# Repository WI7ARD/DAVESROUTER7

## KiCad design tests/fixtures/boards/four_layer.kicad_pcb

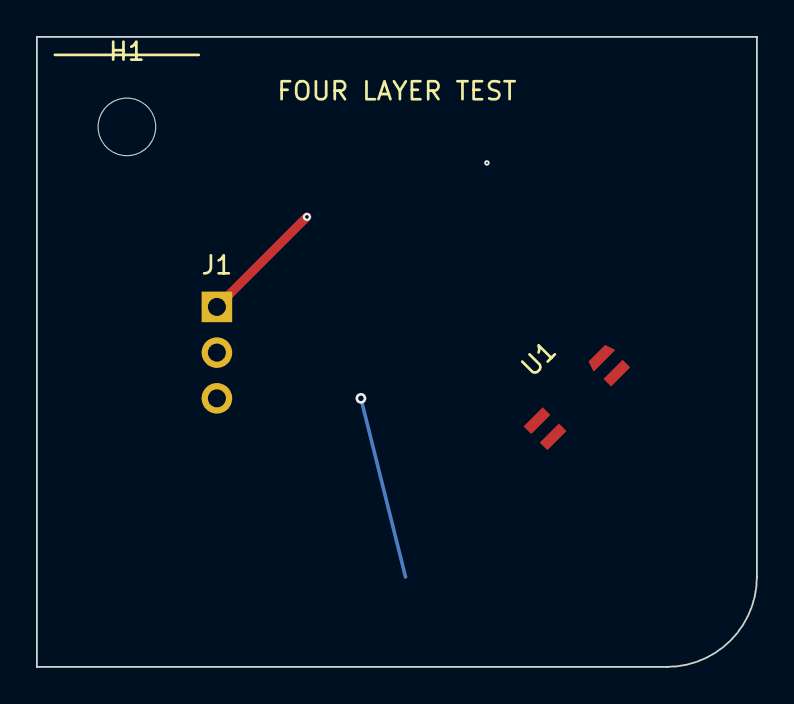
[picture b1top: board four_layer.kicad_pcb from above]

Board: 4 copper layers, 40.0 x 35.0 mm, 4 parts (1 on the bottom side), 3 nets.

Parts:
H1: MountingHole; MountingHole_3.2mm_M3
J1: Conn_01x03; PinHeader_1x03_P2.54mm_Vertical
R2: 4k7; R_0402_1005Metric
U1: SENSOR; SOIC-4_Test

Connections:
+3V3: J1.2, R2.2, U1.1
/DATA: J1.3, R2.1, U1.3
GND: J1.1, U1.2

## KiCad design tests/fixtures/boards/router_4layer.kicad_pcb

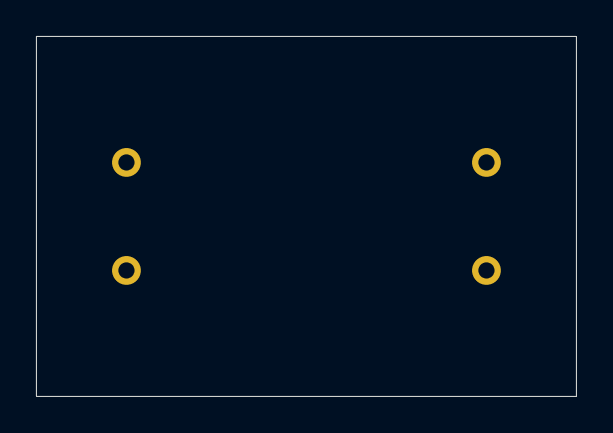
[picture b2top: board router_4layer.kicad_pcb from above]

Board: 4 copper layers, 30.0 x 20.0 mm, 4 parts (0 on the bottom side), 2 nets, no tracks yet.

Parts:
A1, A2: TP
B1, B2: TP

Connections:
N1: A1.1, A2.1
N2: B1.1, B2.1

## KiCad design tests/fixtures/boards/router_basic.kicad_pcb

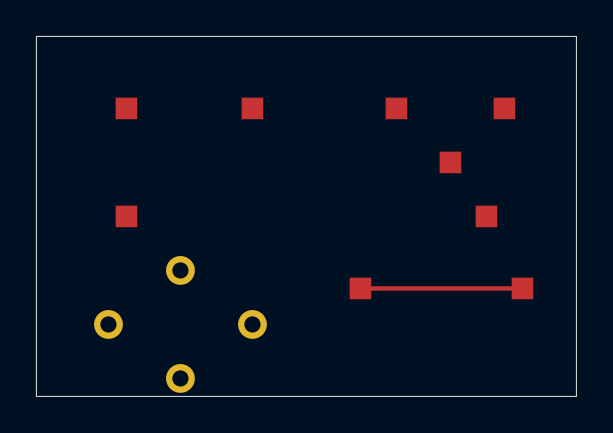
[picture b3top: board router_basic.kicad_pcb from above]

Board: 2 copper layers, 30.0 x 20.0 mm, 13 parts (0 on the bottom side), 6 nets.

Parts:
TP1, TP2, TP3, TP4, TP5, TP6, TP7, TP8, TP9, TP10, TP11, TP12, TP13: TP

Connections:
A: TP1.1, TP2.1
B: TP3.1, TP4.1
C: TP5.1, TP6.1
D: TP7.1, TP8.1
E: TP9.1, TP10.1, TP11.1
G: TP12.1, TP13.1

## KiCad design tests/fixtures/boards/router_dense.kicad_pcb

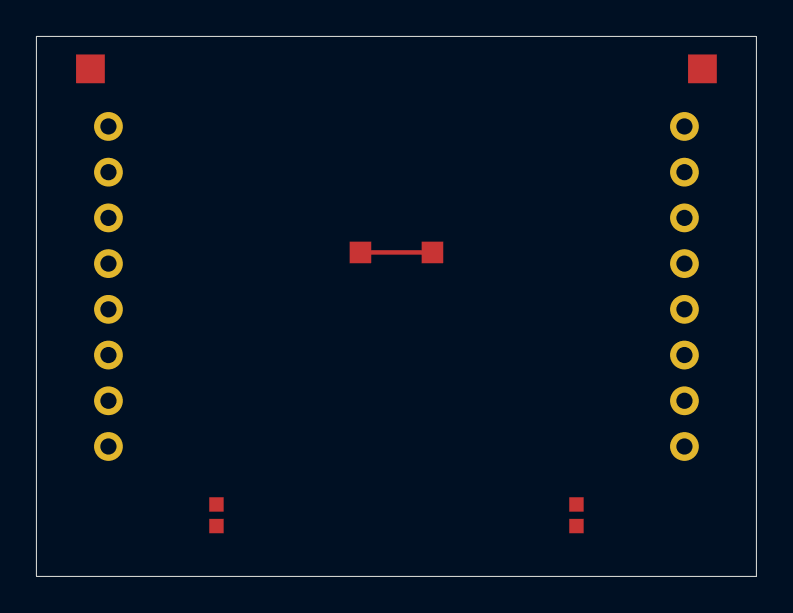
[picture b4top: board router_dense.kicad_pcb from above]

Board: 2 copper layers, 40.0 x 30.0 mm, 24 parts (0 on the bottom side), 12 nets.

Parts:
K1, K2: TP
L0, L1, L2, L3, L4, L5, L6, L7: TP
R0, R1, R2, R3, R4, R5, R6, R7: TP
UN1, UN2: TP
UP1, UP2: TP
V1, V2: TP

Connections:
LOCKED: K1.1, K2.1
S0: L0.1, R0.1
S1: L1.1, R1.1
S2: L2.1, R2.1
S3: L3.1, R3.1
S4: L4.1, R4.1
S5: L5.1, R5.1
S6: L6.1, R6.1
S7: L7.1, R7.1
USB_N: UN1.1, UN2.1
USB_P: UP1.1, UP2.1
VBUS: V1.1, V2.1
